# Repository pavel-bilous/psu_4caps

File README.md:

# Linear PSU board

Resources used to design this board:

* TI application note AN-1849 "An Audio Amplifier Power Supply Design (Rev. C)", 2019 - [link](https://www.ti.com/lit/pdf/snaa057)
* Manufacturers Report - "The Importance of the Power Supply", Nelson Pass, 1997 - [link](https://hometheaterhifi.com/volume_4_2/nelpass.html)
* "Linear Power Supply Design", Rod Elliott, 2001 - [link](https://sound-au.com/power-supplies.htm)
* "Power Supply Design", Tom Christiansen - [link](https://neurochrome.com/pages/power-supply-design)

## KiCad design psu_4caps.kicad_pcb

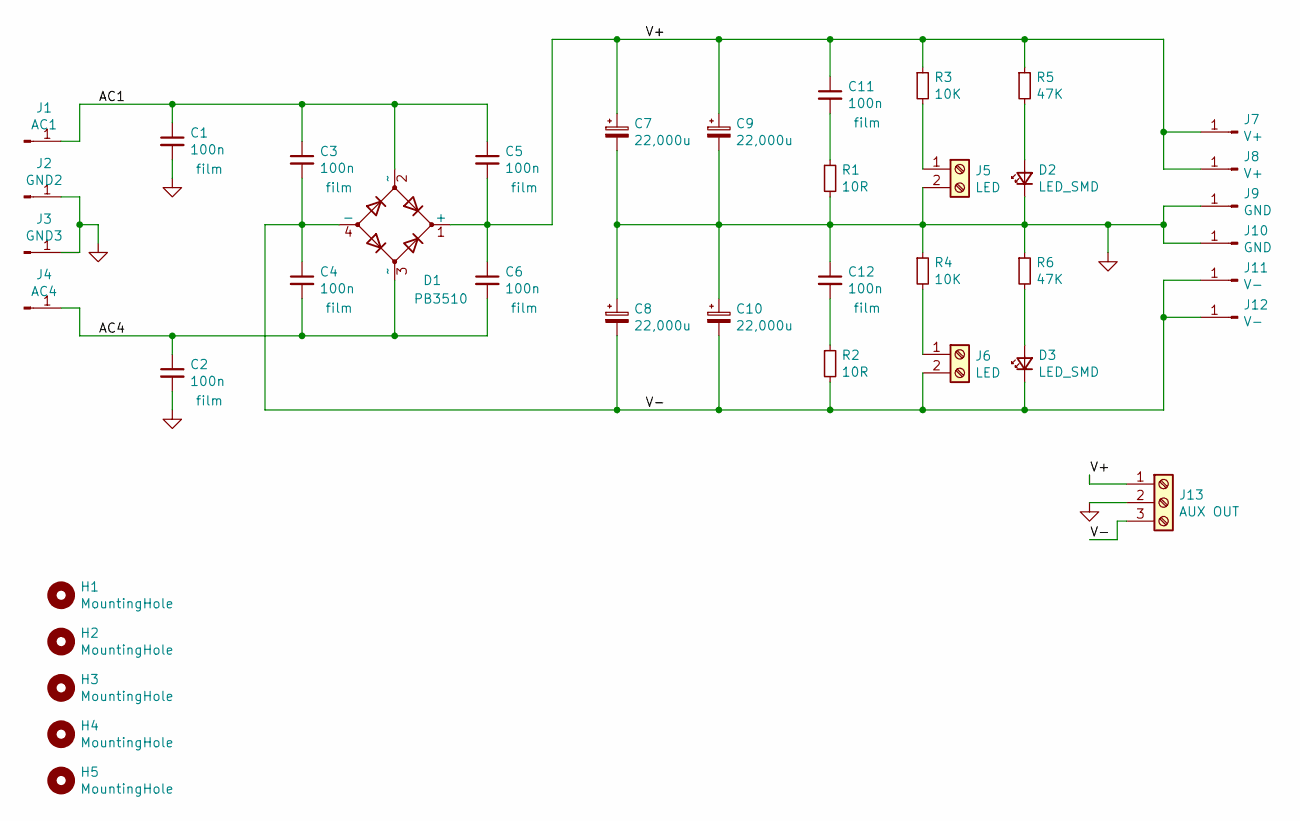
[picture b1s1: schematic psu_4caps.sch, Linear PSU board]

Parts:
C1, C2, C11, C12: 100n; C_Rect_L7.2mm_W2.5mm_P5.00mm_FKS2_FKP2_MKS2_MKP2
C3, C4, C5, C6: 100n; C_Rect_L7.2mm_W4.5mm_P5.00mm_FKS2_FKP2_MKS2_MKP2
C7, C8, C9, C10: 22,000u; CP_Radial_D35.0mm_P10.00mm_SnapIn
D1: PB3510; PB3510E345
D2, D3: LED_SMD; LED_0805_2012Metric_Pad1.15x1.40mm_HandSolder
H1, H2, H3, H4, H5: MountingHole; MountingHole_3.2mm_M3_Pad_Via
J1: AC1; Terminal_.25_PCB_TAB_TE_Connectivity_P5.08mm_
J2: GND2; Terminal_.25_PCB_TAB_TE_Connectivity_P5.08mm_
J3: GND3; Terminal_.25_PCB_TAB_TE_Connectivity_P5.08mm_
J4: AC4; Terminal_.25_PCB_TAB_TE_Connectivity_P5.08mm_
J5, J6: LED; TerminalBlock_MetzConnect_Type059_RT06302HBWC_1x02_P3.50mm_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
J7, J8: V+; Terminal_.25_PCB_TAB_TE_Connectivity_P5.08mm_
J9, J10: GND; Terminal_.25_PCB_TAB_TE_Connectivity_P5.08mm_
J11, J12: V-; Terminal_.25_PCB_TAB_TE_Connectivity_P5.08mm_
J13: AUX OUT; TerminalBlock_ Amphenol_01_03_P3.50mm
R1, R2: 10R; R_Axial_DIN0207_L6.3mm_D2.5mm_P10.16mm_Horizontal
R3, R4: 10K; R_1206_3216Metric_Pad1.42x1.75mm_HandSolder
R5, R6: 47K; R_1206_3216Metric_Pad1.42x1.75mm_HandSolder

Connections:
/AC1: C1.1, C3.1, C5.1, D1.2 (~~), J1.1
/AC4: C2.1, C4.2, C6.2, D1.3 (~~), J4.1
/V+: C5.2, C6.1, C7.1, C9.1, C11.1, D1.1 (+), J7.1, J8.1, J13.1, R3.1, R5.1
/V-: C3.2, C4.1, C8.2, C10.2, D1.4 (-), D3.1 (K), J6.2, J11.1, J12.1, J13.3, R2.2
GND: C1.2, C2.2, C7.2, C8.1, C9.2, C10.1, C12.1, D2.1 (K), J2.1, J3.1, J5.2, J9.1, J10.1, J13.2, R1.2, R4.1, R6.1
unnamed: C11.2, R1.1
unnamed: C12.2, R2.1
unnamed: D2.2 (A), R5.2
unnamed: D3.2 (A), R6.2
unnamed: J5.1, R3.2
unnamed: J6.1, R4.2

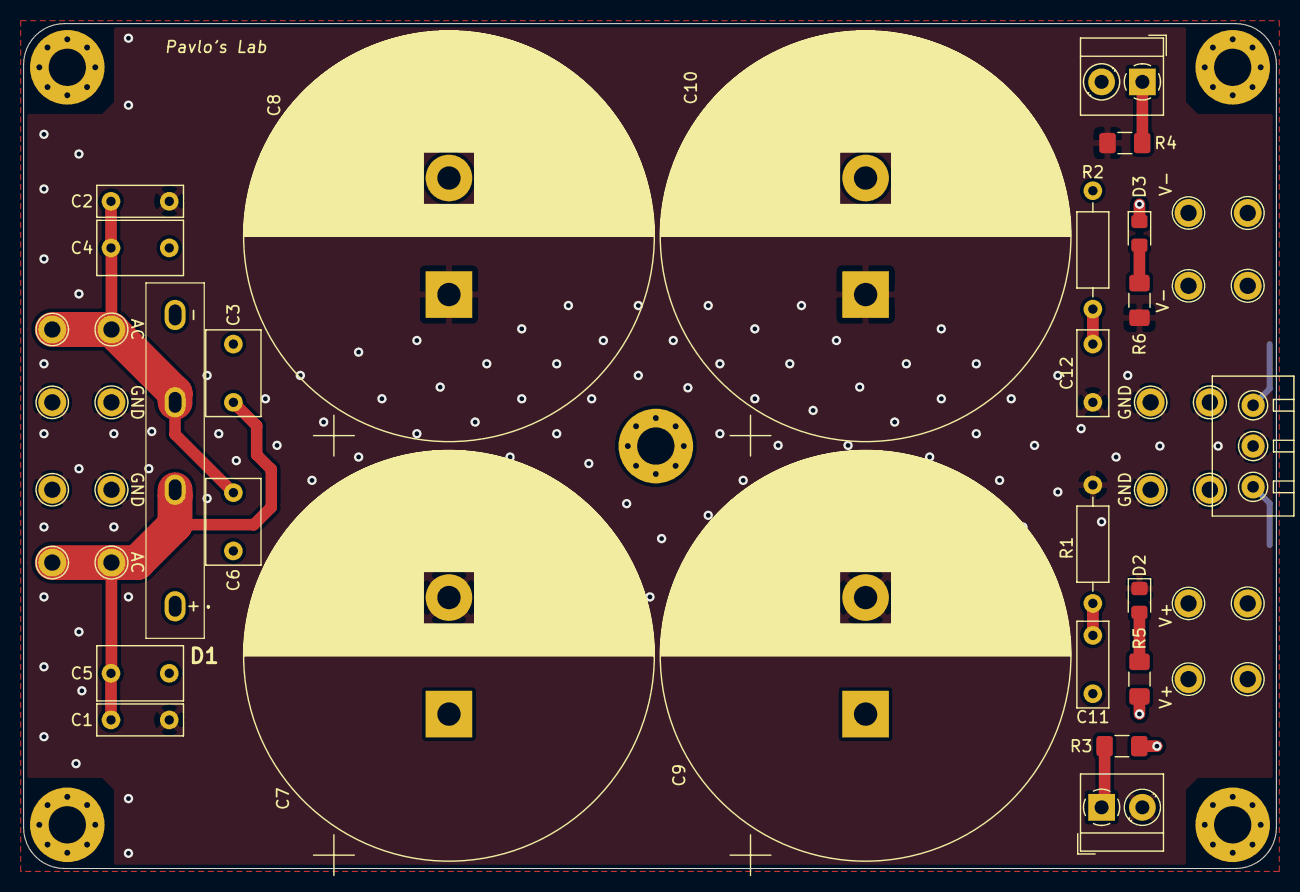
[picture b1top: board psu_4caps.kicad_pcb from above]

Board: 2 copper layers, 107.5 x 72.5 mm, 39 parts (0 on the bottom side), 11 nets.

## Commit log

2024-01-06 finished sch
2024-01-06 finished pcb layout
2024-01-24 rev2 commit
2024-01-26 added bom
